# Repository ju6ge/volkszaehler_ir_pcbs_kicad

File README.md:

Volkszaehler PCB Kicad
======================

This project contains the converted PCB layouts for boards to interact with SML smart meters. The original design are from 'volkszaehler.org'.

Their open designs converted to kicad for further usage with non proprietary software.

## `ir_ttl`

Original Link: https://wiki.volkszaehler.org/hardware/controllers/ir-schreib-lesekopf-ttl-ausgang 

## `ir_rs232`

Original Link:https://wiki.volkszaehler.org/hardware/controllers/ir-schreib-lesekopf-rs232-ausgang

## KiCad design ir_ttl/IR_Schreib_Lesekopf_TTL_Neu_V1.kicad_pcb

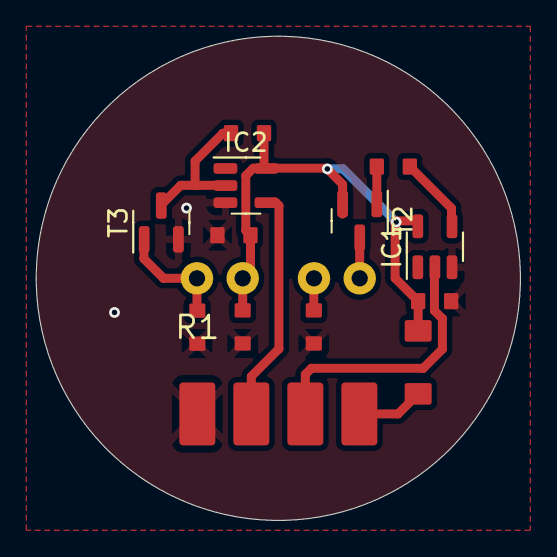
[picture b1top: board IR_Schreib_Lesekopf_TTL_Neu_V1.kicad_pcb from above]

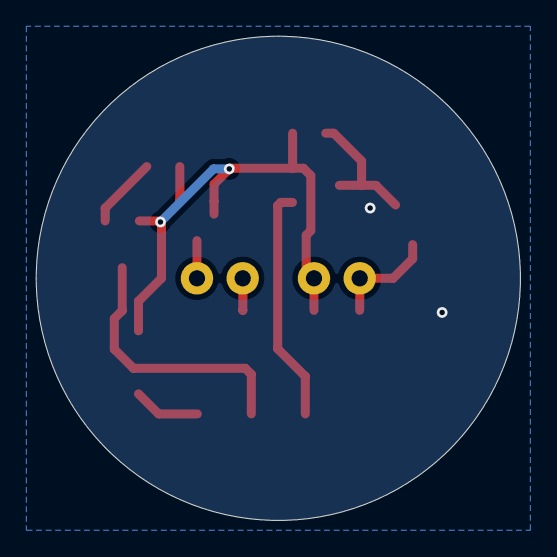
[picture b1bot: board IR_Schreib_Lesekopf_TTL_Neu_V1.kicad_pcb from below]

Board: 2 copper layers, 26.9 x 26.9 mm, 18 parts (2 on the bottom side), 11 nets.

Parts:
C1, C2, C3: 1�F/10V; 0603
D1: SFH487-2; LED_3MM
D2: BAT46W; SOD123
IC1, IC2: 74LVC1G17DBVR; SOT-23-5
R1, R3, R4: 13K/1%; 0603
R2: 180R; 0603
T1: SFH309FA-4; LED_3MM
T2: BC807-40; SOT-23
T3: BC817-40; SOT-23
X1: +Ub; LOETPUNKT
X2: TXD; LOETPUNKT
X3: RXD; LOETPUNKT
X4: GND; LOETPUNKT

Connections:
/VDD: C1.1, C2.1, C3.1, D2.1, IC1.5 (VCC), IC2.5 (VCC), R4.2, T1.2, T2.2 (E)
GND: C1.2, C2.2, C3.2, IC1.3 (GND), IC2.3 (GND), R1.1, R2.2, T3.2 (E), X4.1
unnamed: D1.2, R2.1
unnamed: D2.2, X1.1
unnamed: IC1.2, X2.1
unnamed: IC1.4, R3.1
unnamed: IC2.4, X3.1
unnamed: R3.2, T2.1 (B)
unnamed: D1.1, T2.3 (C)
unnamed: R1.2, T1.1, T3.1 (B)
unnamed: IC2.2, R4.1, T3.3 (C)

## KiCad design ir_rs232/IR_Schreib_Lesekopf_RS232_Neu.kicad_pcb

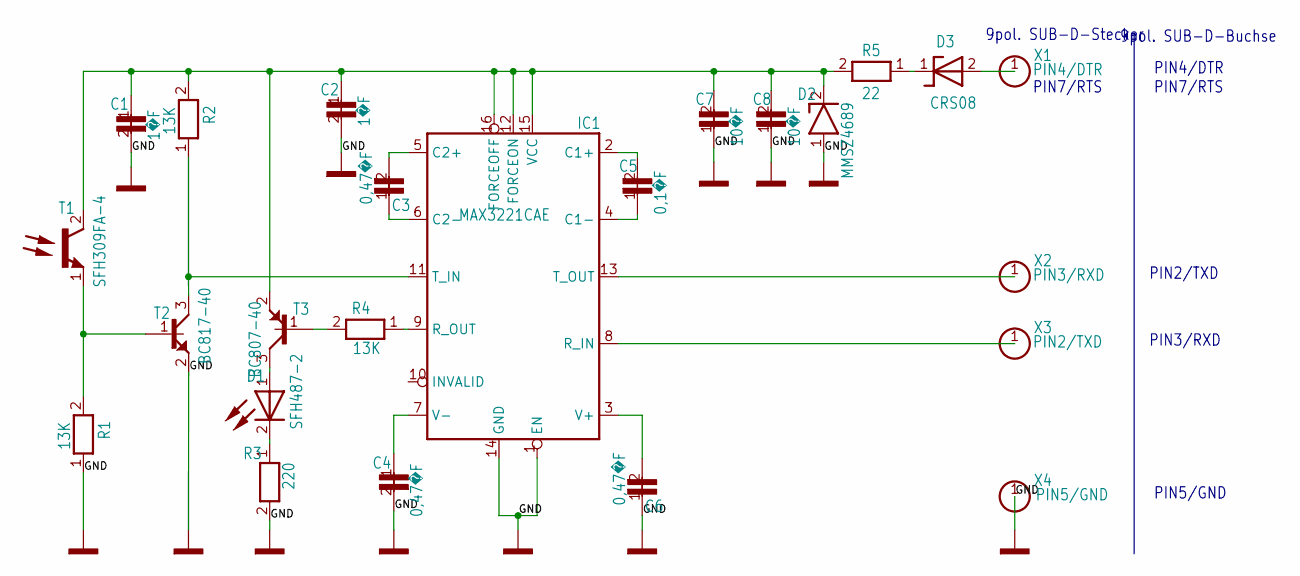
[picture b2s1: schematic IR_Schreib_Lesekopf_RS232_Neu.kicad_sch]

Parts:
C1, C2: 1�F; 0603_KLEIN
C3, C4, C6: 0,47�F; 0603
C5: 0,1�F; 0603
C7, C8: 10�F; 0805_KLEIN
D1: SFH487-2; LED_3MM
D2: MMSZ4689; SOD123
D3: CRS08; SOD123
IC1: MAX3221CAE; SSOP16
R1, R2, R4: 13K; 0603_KLEIN
R3: 220; 0603_KLEIN
R5: 22; 1206
T1: SFH309FA-4; LED_3MM
T2: BC817-40; SOT23_3
T3: BC807-40; SOT23_3
X1: PIN4/DTR; LOETPUNKT
X2: PIN3/RXD; LOETPUNKT
X3: PIN2/TXD; LOETPUNKT
X4: PIN5/GND; LOETPUNKT

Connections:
2: D3.1, R5.1
+: R1.2, T1.1, T2.1
B: R4.2, T3.1
C: D1.1, T3.3
C1+: C5.2, IC1.2 (C1+)
C1-: C5.1, IC1.4 (C1-)
C2+: C3.2, IC1.5 (C2+)
C2-: C3.1, IC1.6 (C2-)
GND: C1.2, C2.2, C4.2, C6.1, C7.1, C8.1, D2.1, IC1.1 (EN), IC1.14 (GND), R1.1, R3.2, T2.2, X4.1
K: D1.2, R3.1
PIN1: D3.2, X1.1
RXD: IC1.11 (T_IN), R2.1, T2.3
R_OUT: IC1.9 (R_OUT), R4.1
SIG$10: IC1.13 (T_OUT), X2.1
SIG$11: IC1.8 (R_IN), X3.1
V+: C6.2, IC1.3 (V+)
V-: C4.1, IC1.7 (V-)
VCC: C1.1, C2.1, C7.2, C8.2, D2.2, IC1.12 (FORCEON), IC1.15 (VCC), IC1.16 (FORCEOFF), R2.2, R5.2, T1.2, T3.2

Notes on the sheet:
PIN2/TXD
PIN7/RTS
PIN4/DTR
9pol. SUB-D-Buchse
9pol. SUB-D-Stecker
PIN5/GND
PIN3/RXD

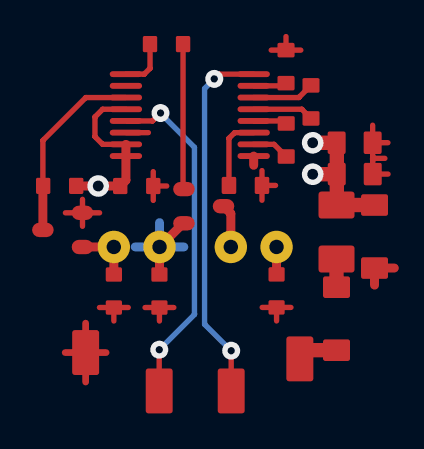
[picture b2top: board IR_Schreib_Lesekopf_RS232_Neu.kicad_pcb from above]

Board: 2 copper layers, 24 parts (1 on the bottom side), 18 nets.

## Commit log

2023-07-12 Initial conversion
2023-07-16 updated some footprints and cutouts WIP
2023-07-19 ir_ttl passing DRC
